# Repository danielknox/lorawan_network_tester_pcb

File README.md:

# lorawan_network_tester_pcb
PCB for the lorawan network tester.

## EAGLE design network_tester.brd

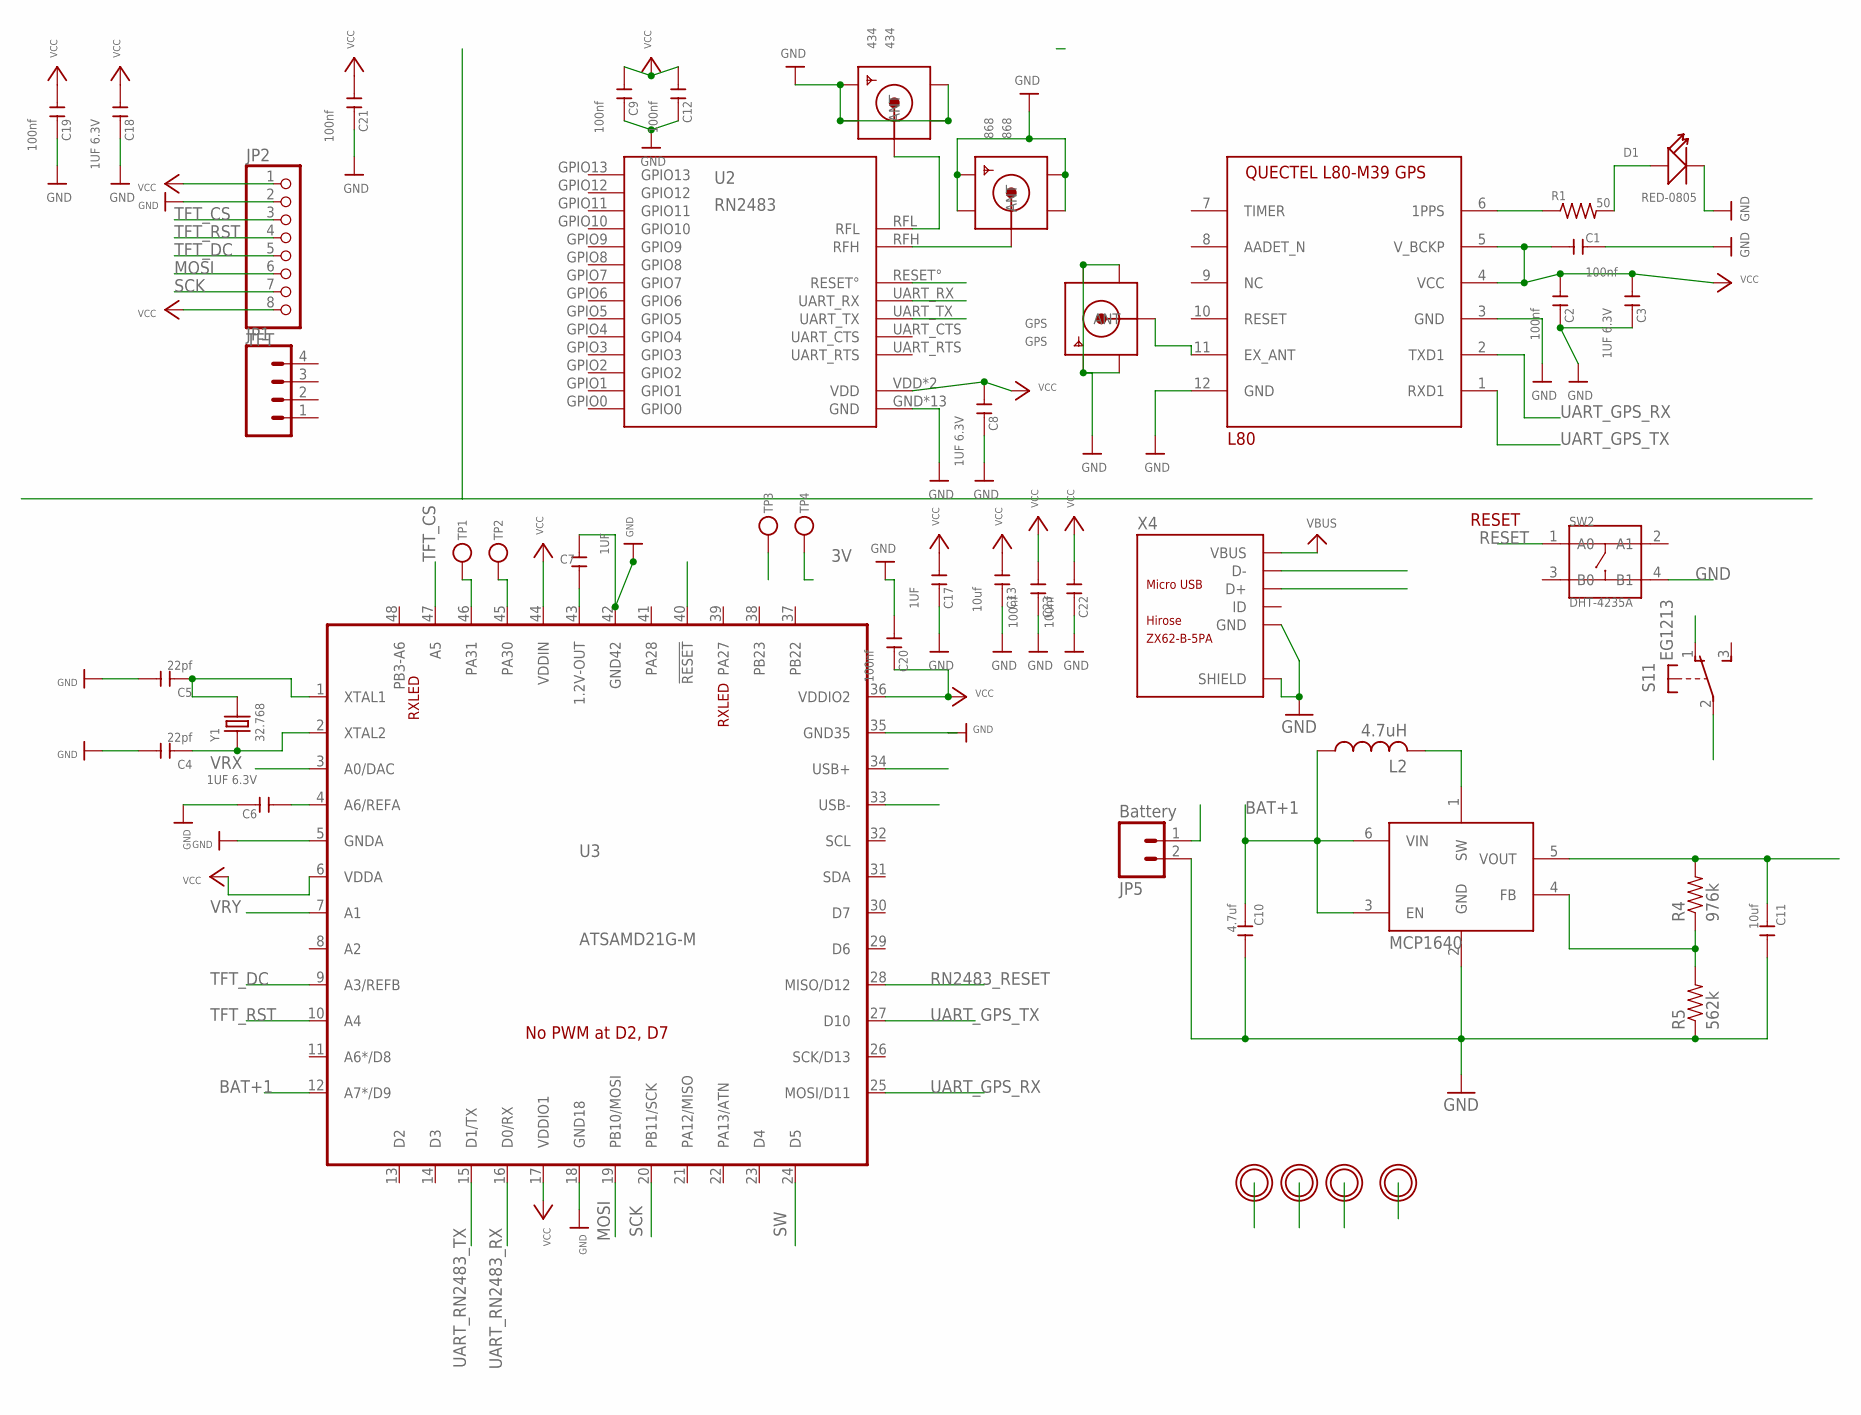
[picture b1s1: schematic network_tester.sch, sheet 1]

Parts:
434: 434; SMA_EDGELAUNCH_UFL
868: 868; SMA_EDGELAUNCH_UFL
C1, C2, C9, C12, C19, C20, C21, C22, C23: 100nf; C0402
C3, C6, C8, C18: 1UF 6.3V; C0402
C4, C5: 22pf; C0402
C7, C17: 1UF; C0402
C10: 4.7uf; C0402
C11, C13: 10uf; C0402
D1: RED-0805; LED-0805
GPS: GPS; SMA_EDGELAUNCH_UFL
H1, H2, H3, H4: MOUNTINGHOLE2.5; MOUNTINGHOLE_2.5_PLATED
JP1: M04PTH; 1X04
JP2: TFT; 1X08-BIG
JP5: Battery; 1X02
L2: 4.7uH; LQH44
L80: L80; L80_PACKAGE
R1: 50; R0805
R4: 976k; 0805
R5: 562k; 0805
S1: EG1213
SW2: DHT-4235A; SW4-SMD-4.2X3.2X2.5MM
TP1, TP2, TP3, TP4: TESTPOINTROUND1.5MM; TESTPOINT_ROUND_1.5MM
U2: RN2483
U3: ATSAMD21G-M; QFN-48
U5: MCP1640; SOT23-6
X4: ZX62-B-5PA; MICRO-USB5+6P-SMD-0.65-AB
Y1: 32.768; X2-SMD-L2.0X1.2X0.55MM

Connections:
3V: C1.1, C2.1, C3.1, C8.1, C9.1, C11.1, C12.1, C13.1, C17.1, C18.1, C19.1, C20.2, C21.1, C22.1, C23.1, JP2.1, JP2.8, L80.4 (VCC), L80.5 (V_BCKP), R4.2, TP4.P$1, U2.VDD, U2.VDD2 (VDD), U3.6 (VDDA), U3.17 (VDDIO1), U3.36 (VDDIO2), U3.44 (VDDIN), U5.5 (VOUT); also elsewhere on the board
BAT+1: C10.1, L2.P$1 (1), S1.2, U3.12 (A7*/D9), U5.3 (EN), U5.6 (VIN)
D+: U3.34 (USB+), X4.3 (D+)
D-: U3.33 (USB-), X4.2 (D-)
GND: 434.GND@1 (GND1), 434.GND@2 (GND2), 434.GND@3 (GND3), 434.GND@4 (GND4), 868.GND@1 (GND1), 868.GND@2 (GND2), 868.GND@3 (GND3), 868.GND@4 (GND4), C1.2, C2.2, C3.2, C4.2, C5.2, C6.2, C7.2, C8.2, C9.2, C10.2, C11.2, C12.2, C13.2, C17.2, C18.2, C19.2, C20.1, C21.2, C22.2, C23.2, D1.-, GPS.GND@1 (GND1), GPS.GND@2 (GND2), GPS.GND@3 (GND3), GPS.GND@4 (GND4), JP2.2, JP5.2, L80.3 (GND), L80.12 (GND), R5.1, SW2.4 (B1), TP3.P$1, U2.GND, U2.GND1 (GND), U2.GND2 (GND), U2.GND3 (GND), U2.GND4 (GND), U2.GND5 (GND), U2.GND6 (GND), U2.GND7 (GND), U2.GND8 (GND), U2.GND9 (GND), U2.GND10 (GND), U2.GND11 (GND), U2.GND12 (GND), U3.5 (GNDA), U3.18 (GND18), U3.35 (GND35), U3.42 (GND42), U5.2 (GND), X4.5 (GND), X4.P1 (SHIELD), X4.P2 (SHIELD), X4.P3_1 (SHIELD), X4.P3_2 (SHIELD), X4.P3_3 (SHIELD), X4.P4_1 (SHIELD), X4.P4_2 (SHIELD), X4.P4_3 (SHIELD), X4.P5 (SHIELD), X4.P6 (SHIELD); also elsewhere on the board
MOSI: JP2.6, U3.19 (PB10/MOSI)
unnamed: L80.6 (1PPS), R1.1
unnamed: D1.+, R1.2
unnamed: C4.1, U3.2 (XTAL2), Y1.1
unnamed: C7.1, U3.43 (1.2V-OUT)
unnamed: 868.P (ANT), U2.RFH
unnamed: C5.1, U3.1 (XTAL1), Y1.2
unnamed: C6.1, U3.4 (A6/REFA)
unnamed: TP1.P$1, U3.46 (PA31)
unnamed: TP2.P$1, U3.45 (PA30)
unnamed: 434.P (ANT), U2.RFL
unnamed: L2.P$2 (2), U5.1 (SW)
unnamed: R4.1, R5.2, U5.4 (FB)
unnamed: GPS.P (ANT), L80.11 (EX_ANT)
PWRIN: JP5.1, S1.1 (O)
RESET: SW2.1 (A0), U3.40 (!RESET!)
RN2483_RESET: U2.RESET°, U3.28 (MISO/D12)
SCK: JP2.7, U3.20 (PB11/SCK)
SW: U3.24 (D5); also elsewhere on the board
TFT_CS: JP2.3, U3.47 (A5)
TFT_DC: JP2.5, U3.9 (A3/REFB)
TFT_RST: JP2.4, U3.10 (A4)
UART_GPS_RX: L80.2 (TXD1), U3.25 (MOSI/D11)
UART_GPS_TX: L80.1 (RXD1), U3.27 (D10)
UART_RN2483_RX: U2.UART_TX, U3.16 (D0/RX)
UART_RN2483_TX: U2.UART_RX, U3.15 (D1/TX)
VBUS: X4.1 (VBUS)
VRX: U3.3 (A0/DAC); also elsewhere on the board
VRY: U3.7 (A1); also elsewhere on the board

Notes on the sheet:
RESET

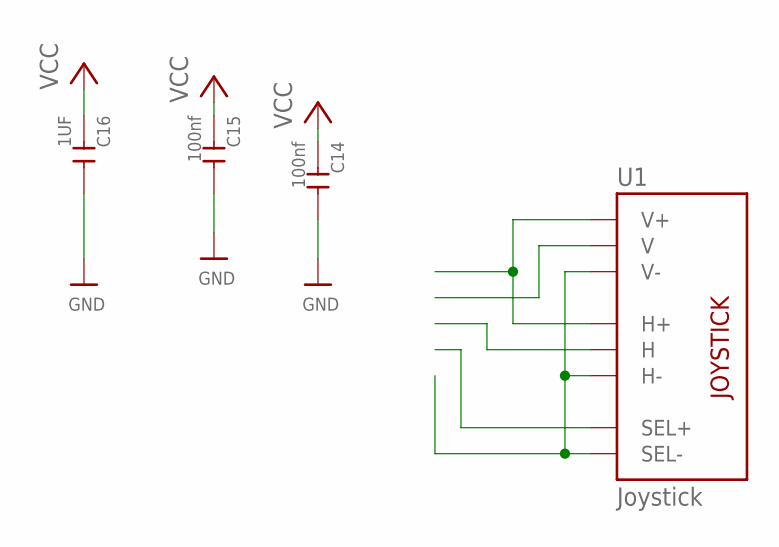
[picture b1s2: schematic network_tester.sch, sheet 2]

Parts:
C14, C15: 100nf; C0402
C16: 1UF; C0402
U1: Joystick; JOYSTICK

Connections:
3V: C14.1, C15.1, C16.1, U1.H1 (H+), U1.V1 (V+); also elsewhere on the board
GND: C14.2, C15.2, C16.2, U1.B2A (SEL-), U1.H3 (H-), U1.V3 (V-); also elsewhere on the board
SW: U1.B1A (SEL+); also elsewhere on the board
VRX: U1.H2 (H); also elsewhere on the board
VRY: U1.V2 (V); also elsewhere on the board

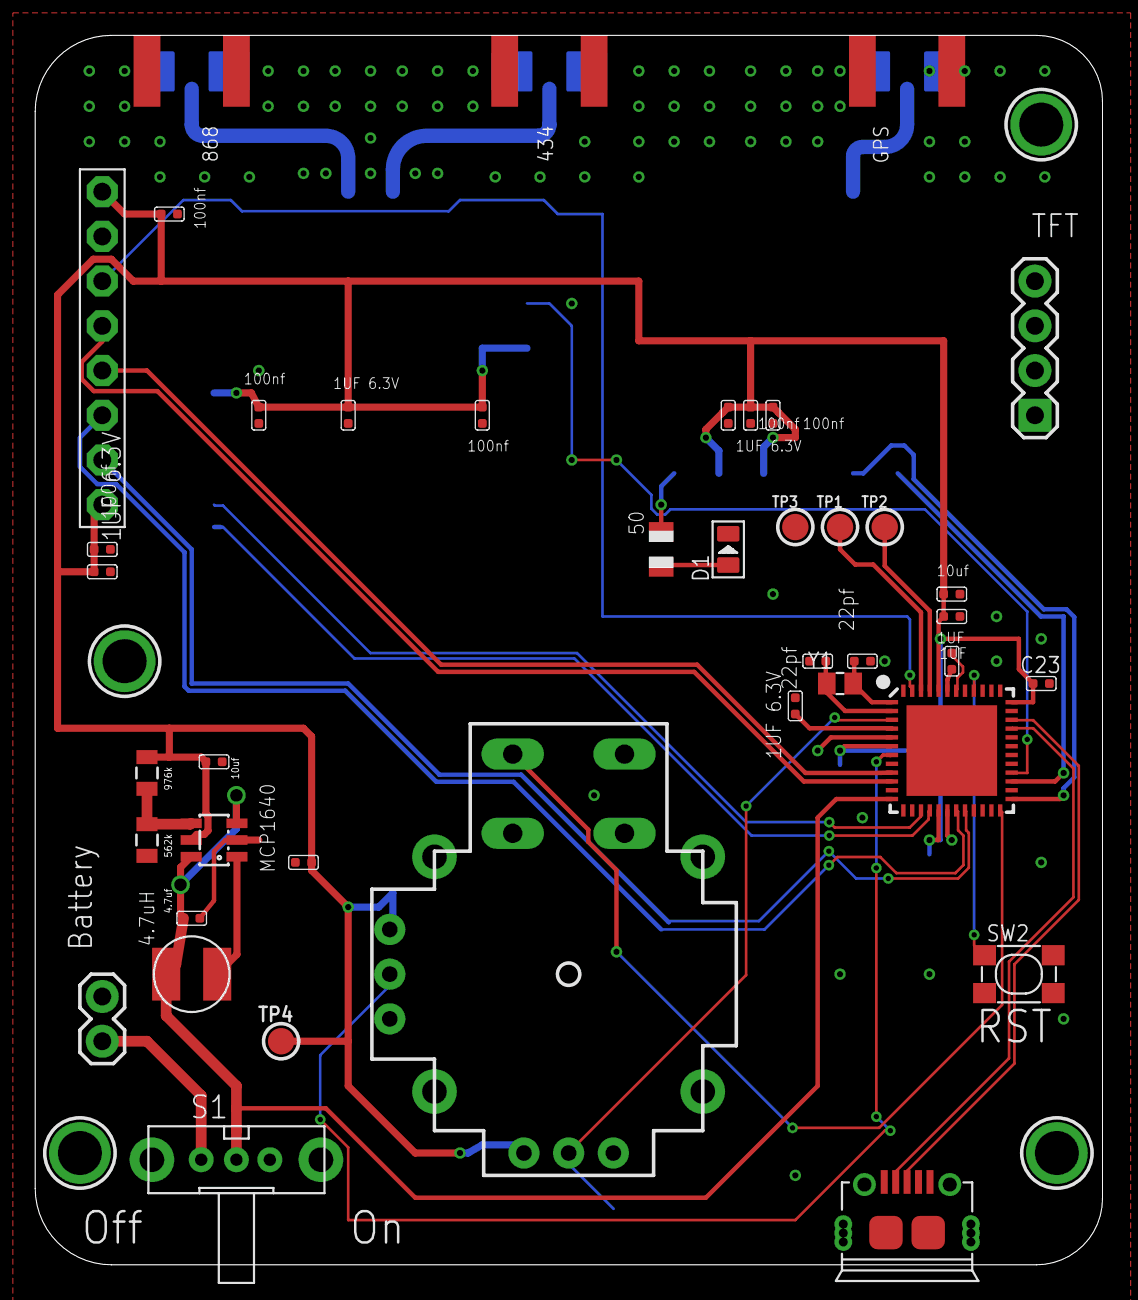
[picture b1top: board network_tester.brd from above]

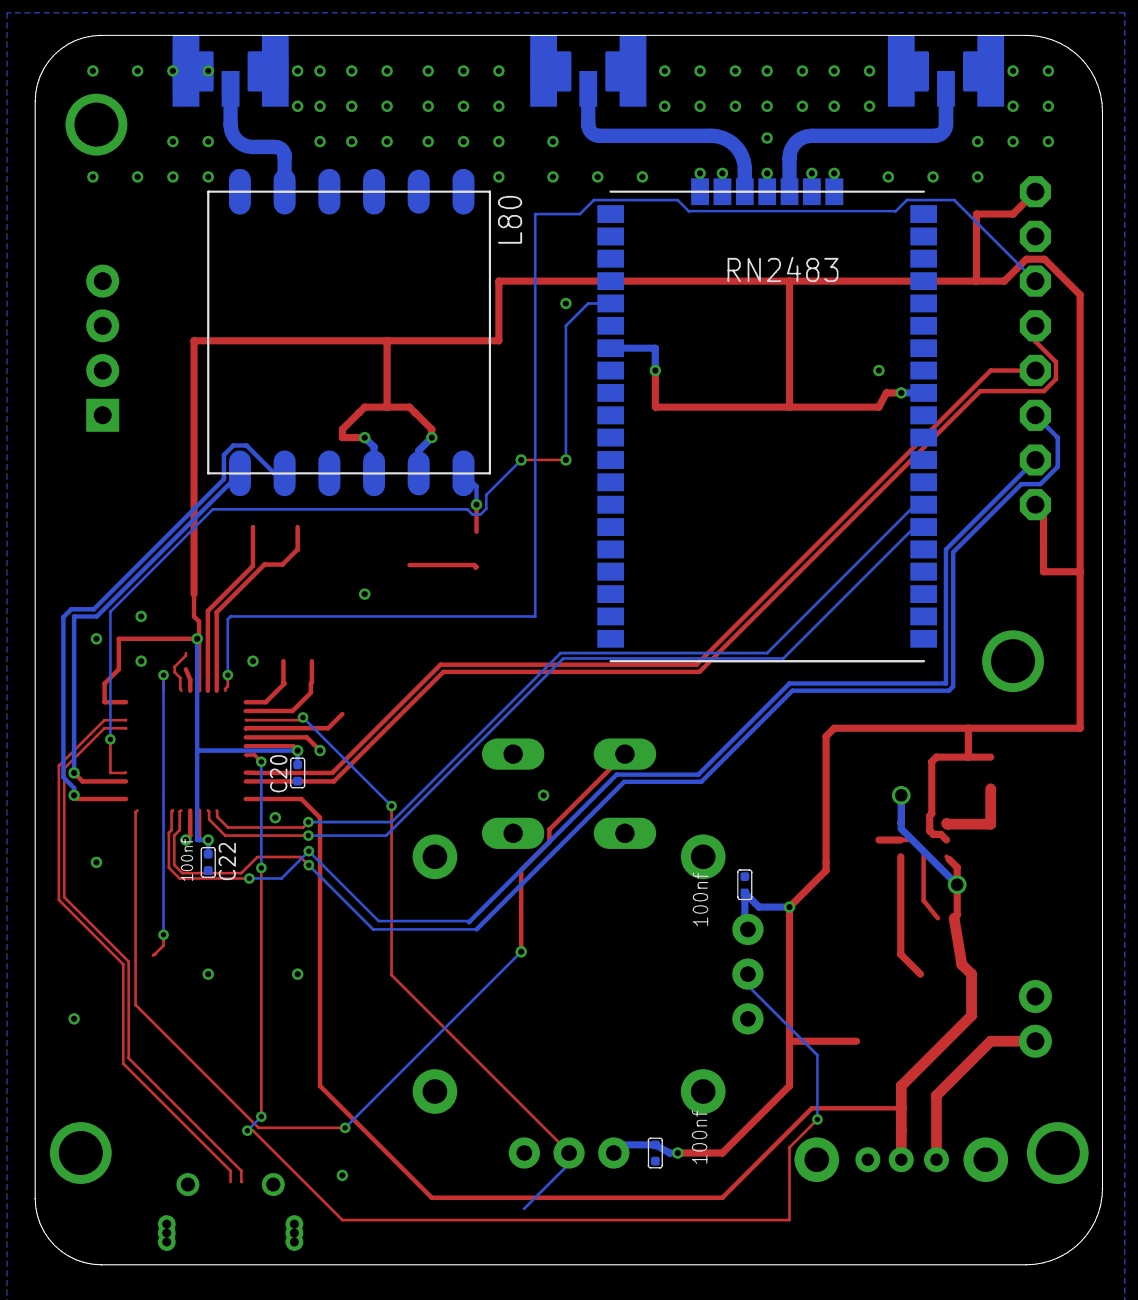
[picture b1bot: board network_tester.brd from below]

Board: 2 copper layers, 60.6 x 69.8 mm, 51 parts (9 on the bottom side), 33 nets.

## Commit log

2018-09-12 Test points added, fixed board labels
2018-09-12 fixed board labels
2018-09-17 test point resolved
2018-09-19 initial bom file
2018-09-19 First commit of board for external fabbing -- untested

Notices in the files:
parts and their libraries:
SparkFun-Connectors: Licensing: CC v3.0 Share-Alike You are welcome to use this library for commercial purposes.
